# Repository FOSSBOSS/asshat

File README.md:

# asshat
DONT BE LIKE THAT> 
Assistant Hat to provide analog pots and 24Vdc switching to devices youll connect to a PI. Intent: control a PLC via a Raspberry Pi by simulating inputs.

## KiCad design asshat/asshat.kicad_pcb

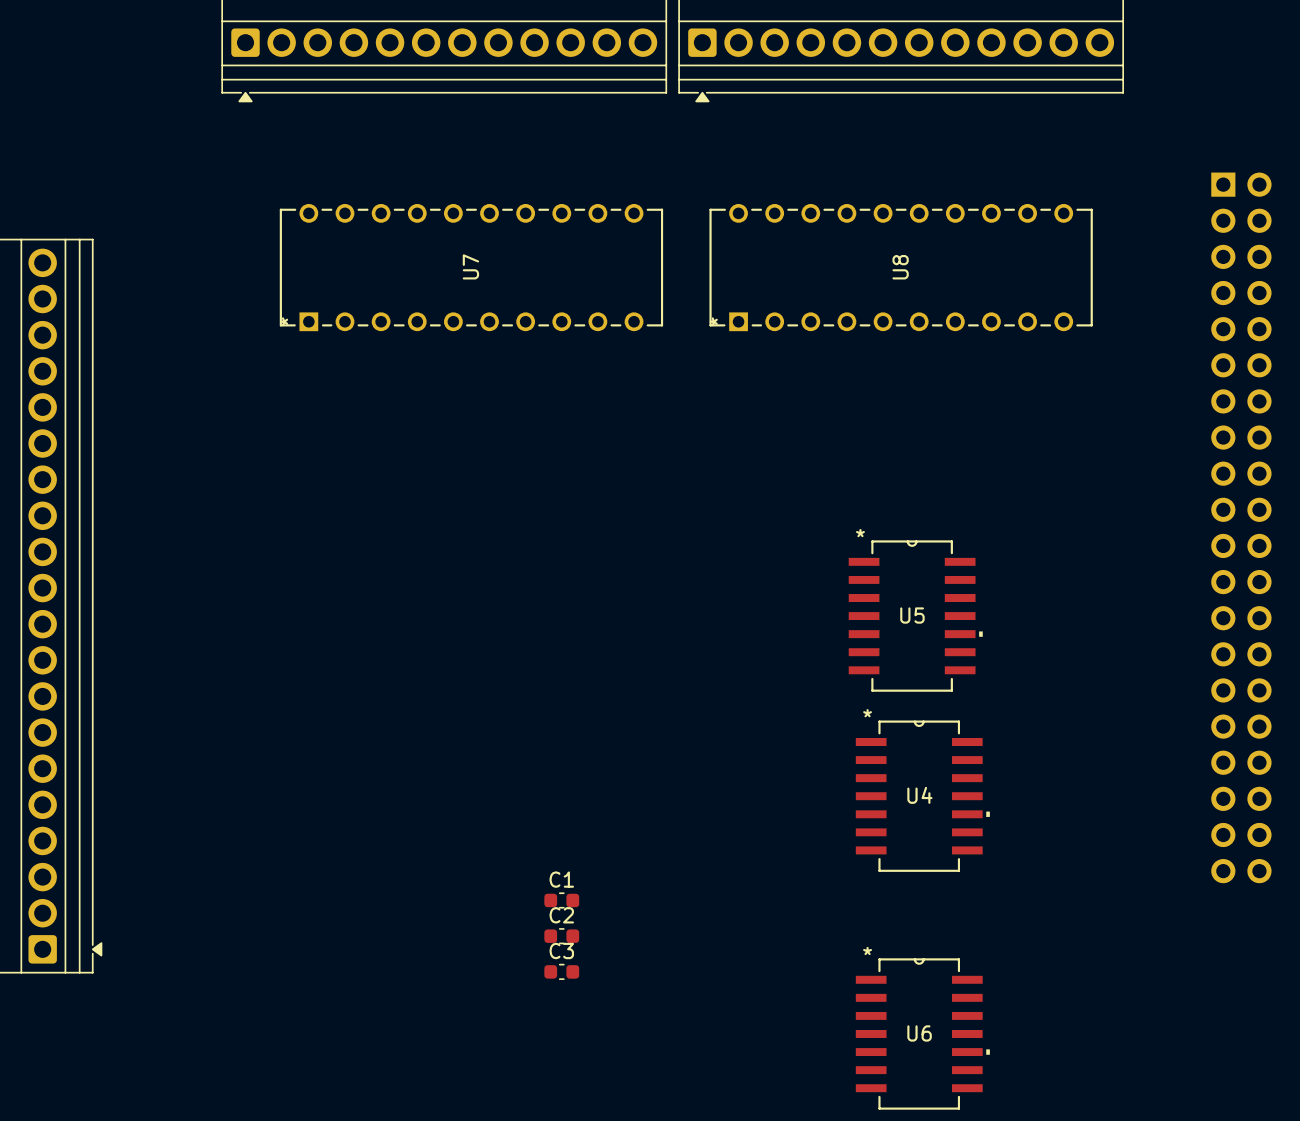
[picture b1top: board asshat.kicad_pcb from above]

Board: 2 copper layers, 12 parts (1 on the bottom side), 41 nets, no tracks yet.

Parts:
C1, C2, C3: C; C_0603_1608Metric
J1: Conn_02x20_Odd_Even; PinSocket_2x20_P2.54mm_Vertical
J2: Screw_Terminal_01x20; TerminalBlock_Xinya_XY308-2.54-20P_1x20_P2.54mm_Horizontal
J3, J4: Screw_Terminal_01x12; TerminalBlock_Xinya_XY308-2.54-12P_1x12_P2.54mm_Horizontal
U4, U5, U6: 74AHCT125; SN74AHCT125NSR_NS14
U7: MAX333A; MAX333CPP_
U8: MAX333; MAX333CPP_

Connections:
/ls1: J1.36, U5.2
/ls2: J1.11, U5.5
/ls3: J1.13, U5.9
/ls4: J1.15, U5.12
/ls5: J1.29, U6.2
/ls6: J1.31, U6.5
/ls7: J1.33, U6.9
/ls8: J1.35, U6.12
/nc1: J3.2, U7.4
/nc2: J3.5, U7.7
/nc3: J3.7, J3.8, U7.13, U7.14
/nc4: J3.11, U7.17
/nc5: J4.2, U8.4
/nc6: J4.5, U8.7
/nc7: J4.8, U8.14
/nc8: J4.11, U8.17
/no1: J3.3, U7.2
/no2: J3.6, U7.9
/no3: J3.9, U7.12
/no4: J3.12, U7.19
/no5: J4.3, U8.2
/no6: J4.6, U8.9
/no7: J4.9, U8.12
/no8: J4.12, U8.19
/oc1: J3.1, U7.3
/oc2: J3.4, U7.8
/oc4: J3.10, U7.18
/oc5: J4.1, U8.3
/oc6: J4.4, U8.8
/oc7: J4.7, U8.13
/oc8: J4.10, U8.18
/sw1: U5.3, U7.1
/sw2: U5.6, U7.10
/sw3: U5.8, U7.11
/sw4: U5.11, U7.20
/sw5: U6.3, U8.1
/sw6: U6.6, U8.10
/sw7: U6.8, U8.11
/sw8: U6.11, U8.20
GND: C1.2, C2.1, C3.1, J1.6, J1.39, J2.1, J2.20, U4.7 (GND), U5.1, U5.4, U5.7 (GND), U5.10, U5.13, U6.1, U6.4, U6.7 (GND), U6.10, U6.13, U7.5 (V-), U7.6 (GND), U8.5 (V-), U8.6 (GND)
VCC: C1.1, C2.2, C3.2, J1.2, J1.4, U4.14 (VCC), U5.14 (VCC), U6.14 (VCC), U7.16 (V+), U8.16 (V+)

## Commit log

2025-07-31 inaugural commit
    nothing works lol. but it is all there. Ive built it already, as a prototype, but not a Pi hat.
